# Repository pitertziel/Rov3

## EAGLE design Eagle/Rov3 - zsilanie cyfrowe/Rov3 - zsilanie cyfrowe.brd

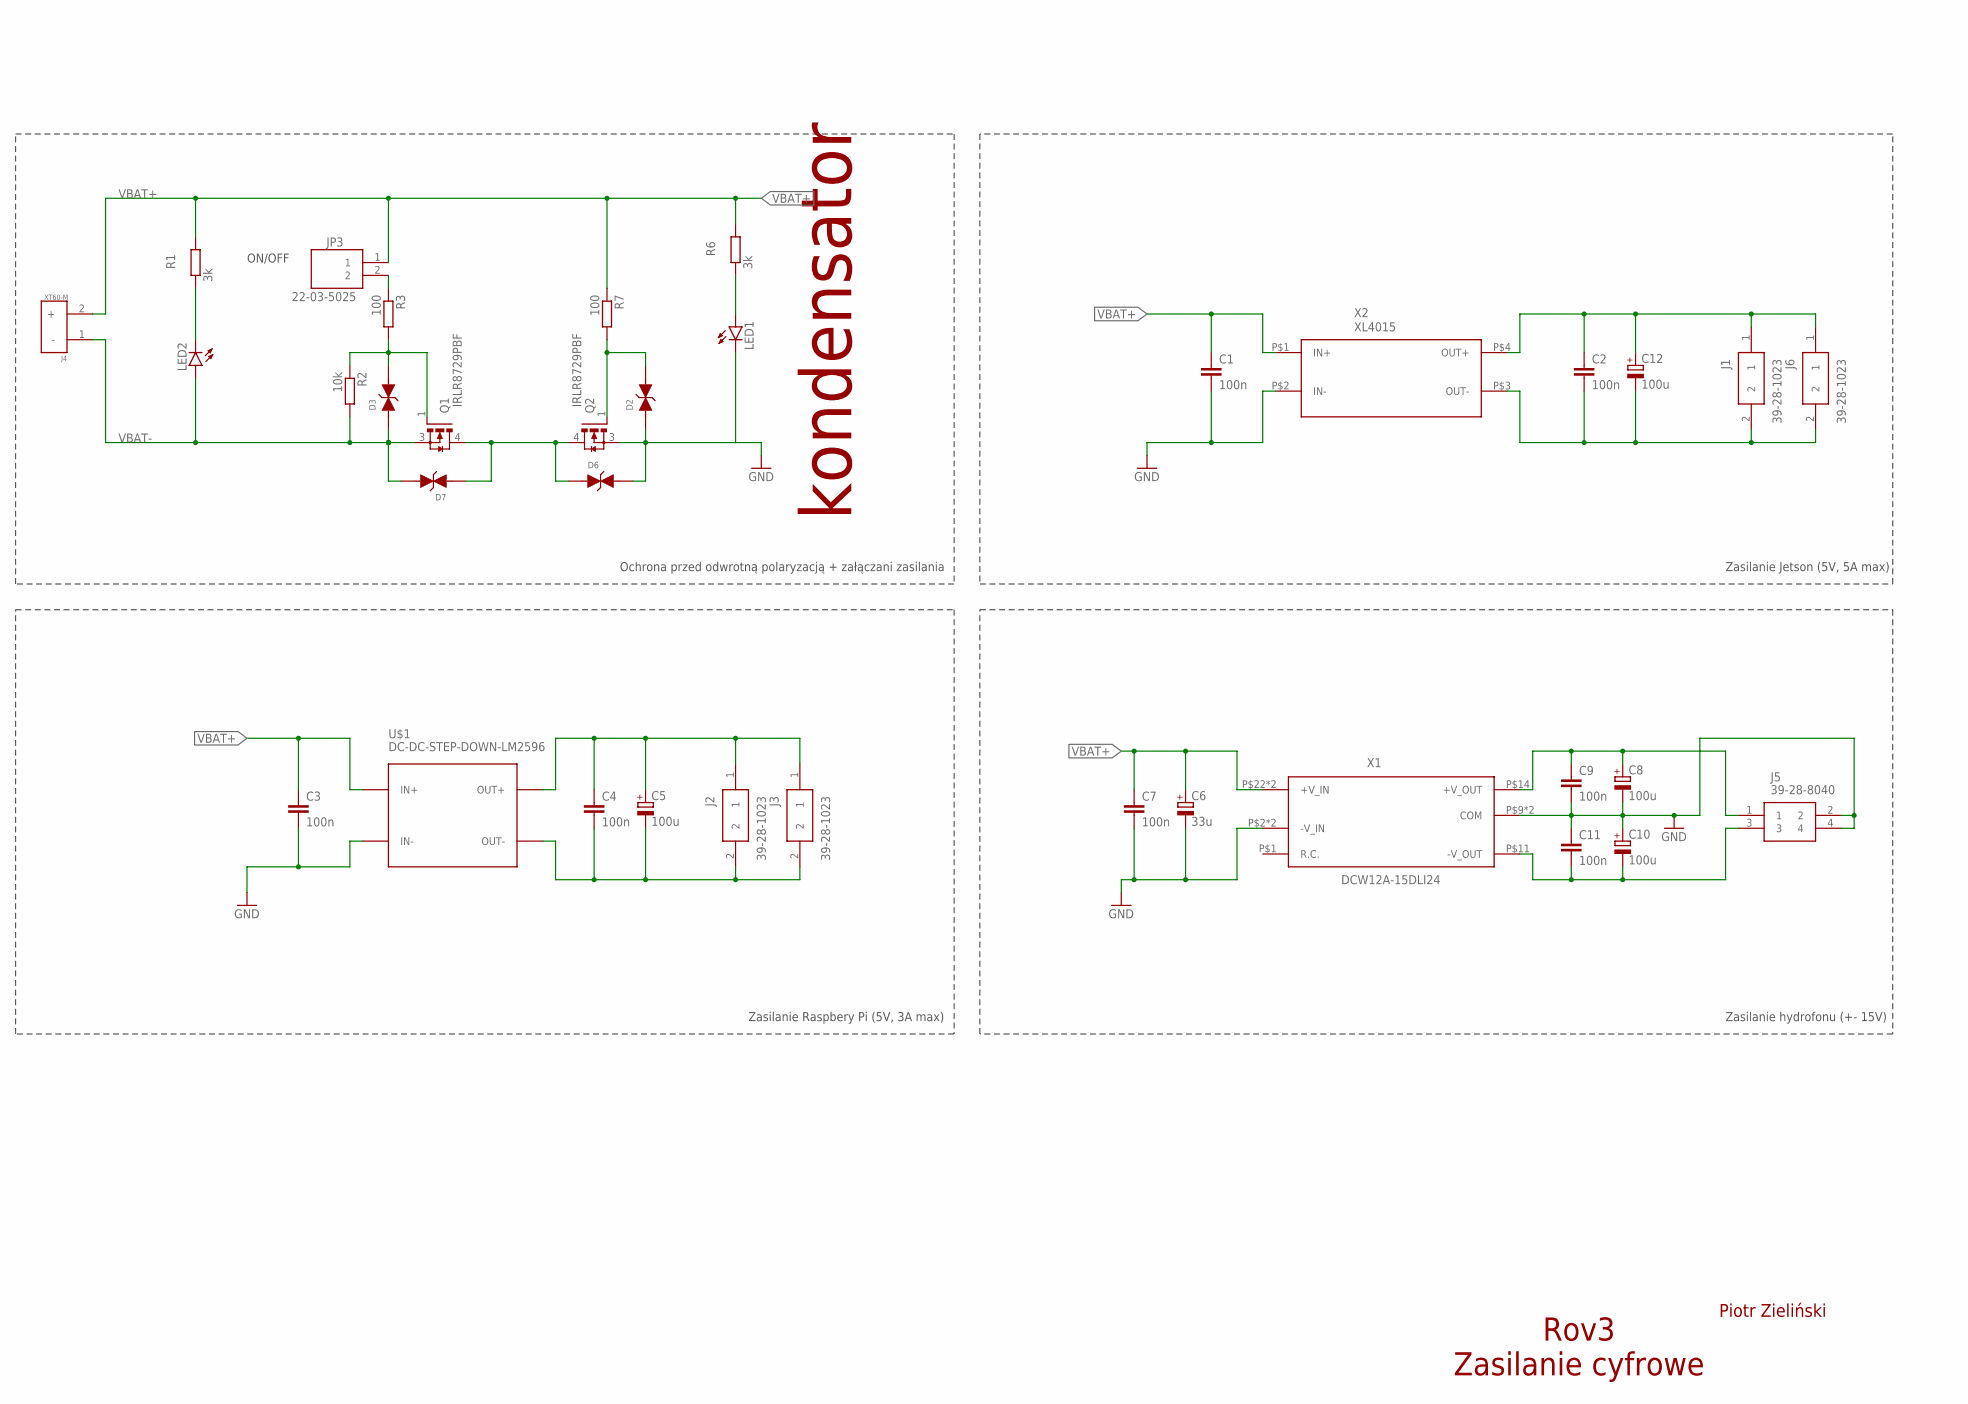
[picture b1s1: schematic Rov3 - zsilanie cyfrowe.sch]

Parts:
C1, C2, C3, C4, C7, C9, C11: 100n; C0805
C5, C8, C10, C12: 100u; E3,5-8
C6: 33u; E3,5-8
D2, D3, D6, D7: P6SMB20A_824501101; VARTVSP_SMA/DO-214AC
J1, J2, J3, J6: 39-28-1023; MOLEX_1X2_PCB_SOCKET
J4: XT60-M; AMASS_XT60-M
J5: 39-28-8040; MOLEX_2X2_PCB_SOCKET
JP3: 22-03-5025; 2.50MM_MINI-SPOX_2PIN_PCB_SOCKET
LED1, LED2: LEDCHIP-LED0805; CHIP-LED0805
Q1, Q2: IRLR8729PBF; DPAK
R1, R6: 3k; R1206
R2: 10k; R1206
R3, R7: 100; R1206
U$1: DC-DC-STEP-DOWN-LM2596
X1: DCW12A-15DLI24; DCW12A-15
X2: XL4015

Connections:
2596+: C4.1, C5.+, J2.1, J3.1, U$1.OUT+
2596-: C4.2, C5.-, J2.2, J3.2, U$1.OUT-
4015+: C2.1, C12.+, J1.1, J6.1, X2.P$4 (OUT+)
4015-: C2.2, C12.-, J1.2, J6.2, X2.P$3 (OUT-)
DCW_+15: C8.+, C9.1, J5.1, X1.P$14 (+V_OUT)
DCW_-15: C10.-, C11.2, J5.3, X1.P$11 (-V_OUT)
GND: C1.2, C3.2, C6.-, C7.2, C8.-, C9.2, C10.+, C11.1, D2.1, D6.2, J5.2, J5.4, LED1.C, Q2.3 (S), U$1.IN-, X1.P$2 (-V_IN), X1.P$3 (-V_IN), X1.P$9 (COM), X1.P$16 (COM), X2.P$2 (IN-)
unnamed: LED1.A, R6.1
unnamed: JP3.2, R3.1
unnamed: LED2.C, R1.1
Q1_G: D3.2, Q1.1 (G), R2.1, R3.2
Q1_Q2_D: D6.1, D7.1, Q1.4 (D), Q2.4 (D)
Q2G: D2.2, Q2.1 (G), R7.2
VBAT+: C1.1, C3.1, C6.+, C7.1, J4.2 (+), JP3.1, R1.2, R6.2, R7.1, U$1.IN+, X1.P$22 (+V_IN), X1.P$23 (+V_IN), X2.P$1 (IN+)
VBAT-: D3.1, D7.2, J4.1 (-), LED2.A, Q1.3 (S), R2.2

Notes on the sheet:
Rov3 Zasilanie cyfrowe
Piotr Zieliński
ON/OFF
kondensator
Ochrona przed odwrotną polaryzacją + załączani zasilania
Zasilanie Raspbery Pi (5V, 3A max)
Zasilanie Jetson (5V, 5A max)
Zasilanie hydrofonu (+- 15V)

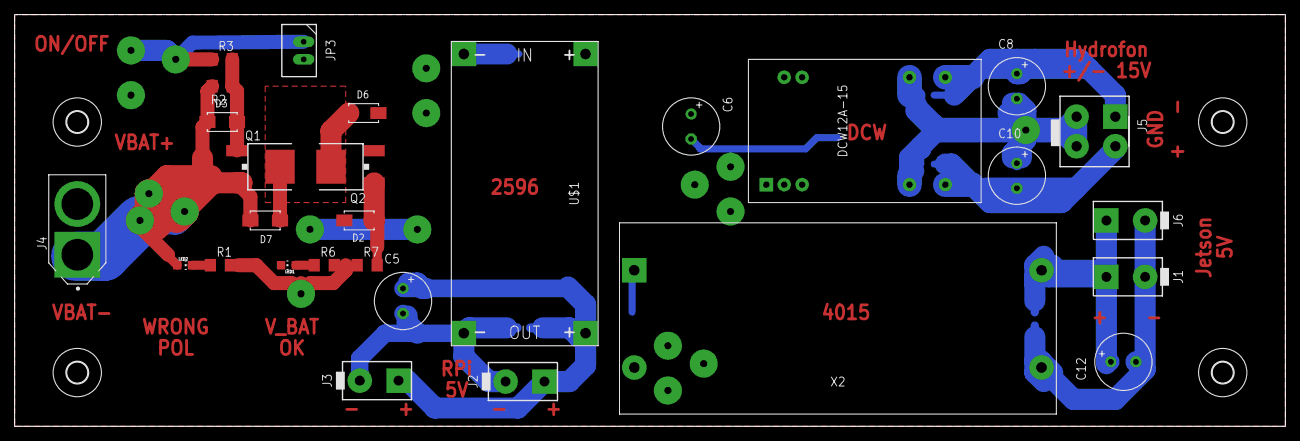
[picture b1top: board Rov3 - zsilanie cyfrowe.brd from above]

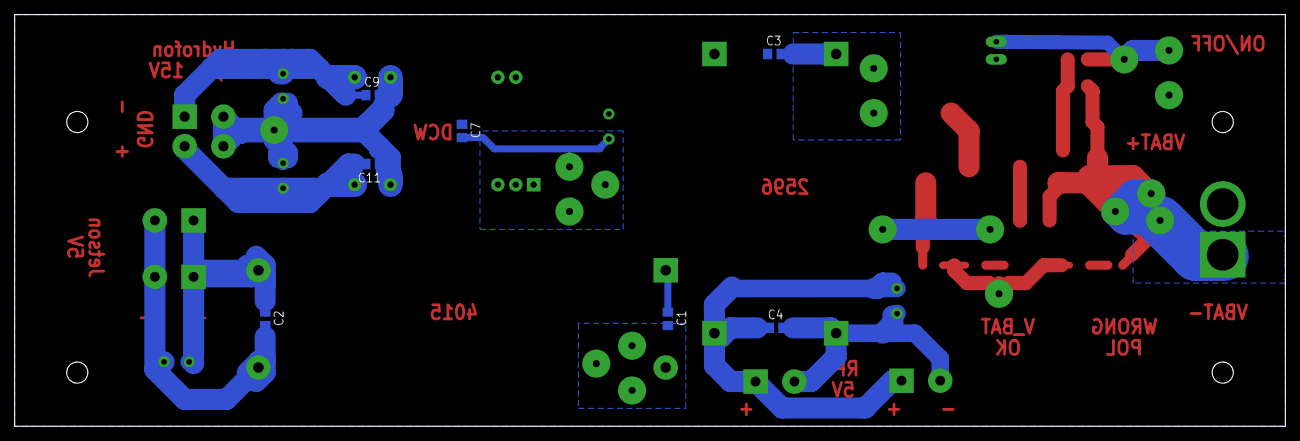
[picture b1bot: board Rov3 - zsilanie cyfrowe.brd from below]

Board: 2 copper layers, 180.3 x 58.4 mm, 39 parts (7 on the bottom side), 15 nets.

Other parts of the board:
U$2, U$3, U$4, U$5: 3,0

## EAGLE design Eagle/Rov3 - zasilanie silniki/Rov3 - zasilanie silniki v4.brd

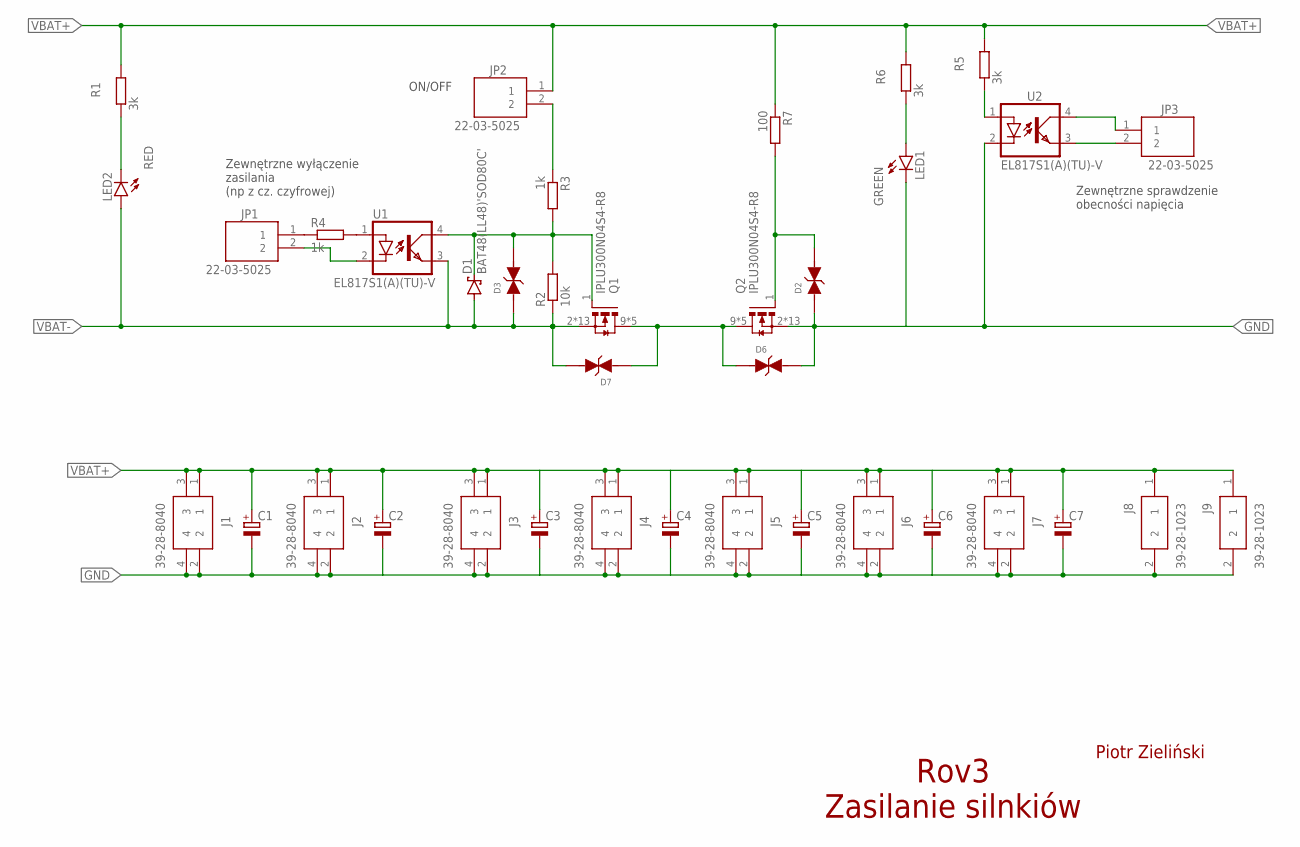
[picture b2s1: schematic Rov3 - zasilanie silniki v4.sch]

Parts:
C1, C2, C3, C4, C5, C6, C7: CPOL-EUE5-10.5; E5-10,5
D1: BAT48(LL48)'SOD80C'; SOD80C
D2, D3, D6, D7: P6SMB20A_824501101; VARTVSP_SMA/DO-214AC
J1, J2, J3, J4, J5, J6, J7: 39-28-8040; MOLEX_2X2_PCB_SOCKET
J8, J9: 39-28-1023; MOLEX_1X2_PCB_SOCKET
JP1, JP2, JP3: 22-03-5025; 2.50MM_MINI-SPOX_2PIN_PCB_SOCKET
LED1: GREEN; CHIP-LED0805
LED2: RED; CHIP-LED0805
Q1, Q2: IPLU300N04S4-R8; PG-HSOF-8-1
R1, R5, R6: 3k; R1206
R2: 10k; R1206
R3, R4: 1k; R1206
R7: 100; R1206
U1, U2: EL817S1(A)(TU)-V; SOIC254P1030X390-4N_EL817S1(A)(TU)-V

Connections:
GND: C1.-, C2.-, C3.-, C4.-, C5.-, C6.-, C7.-, D2.1, D6.2, J1.2, J1.4, J2.2, J2.4, J3.2, J3.4, J4.2, J4.4, J5.2, J5.4, J6.2, J6.4, J7.2, J7.4, J8.2, J9.2, LED1.C, Q2.2 (S), Q2.3 (S), Q2.4 (S), Q2.5 (S), Q2.6 (S), Q2.7 (S), Q2.8 (S), Q2.10 (S), Q2.11 (S), Q2.12 (S), Q2.13 (S), Q2.14 (S), Q2.15 (S), U2.2 (C)
unnamed: LED1.A, R6.1
unnamed: D6.1, D7.1, Q1.9 (D), Q1.16 (D), Q1.17 (D), Q1.18 (D), Q1.19 (D), Q2.9 (D), Q2.16 (D), Q2.17 (D), Q2.18 (D), Q2.19 (D)
unnamed: JP1.1, R4.1
unnamed: D1.C, D3.2, Q1.1 (G), R2.2, R3.2, U1.4 (COL)
unnamed: JP1.2, U1.2 (C)
unnamed: R4.2, U1.1 (A)
unnamed: JP2.2, R3.1
unnamed: JP3.2, U2.3 (EMIT)
unnamed: JP3.1, U2.4 (COL)
unnamed: R5.1, U2.1 (A)
unnamed: LED2.C, R1.1
unnamed: D2.2, Q2.1 (G), R7.2
VBAT+: C1.+, C2.+, C3.+, C4.+, C5.+, C6.+, C7.+, J1.1, J1.3, J2.1, J2.3, J3.1, J3.3, J4.1, J4.3, J5.1, J5.3, J6.1, J6.3, J7.1, J7.3, J8.1, J9.1, JP2.1, R1.2, R5.2, R6.2, R7.1
VBAT-: D1.A, D3.1, D7.2, LED2.A, Q1.2 (S), Q1.3 (S), Q1.4 (S), Q1.5 (S), Q1.6 (S), Q1.7 (S), Q1.8 (S), Q1.10 (S), Q1.11 (S), Q1.12 (S), Q1.13 (S), Q1.14 (S), Q1.15 (S), R2.1, U1.3 (EMIT)

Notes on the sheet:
Rov3 Zasilanie silnkiów
Piotr Zieliński
Zewnętrzne sprawdzenie obecności napięcia
ON/OFF
Zewnętrzne wyłączenie zasilania (np z cz. czyfrowej)

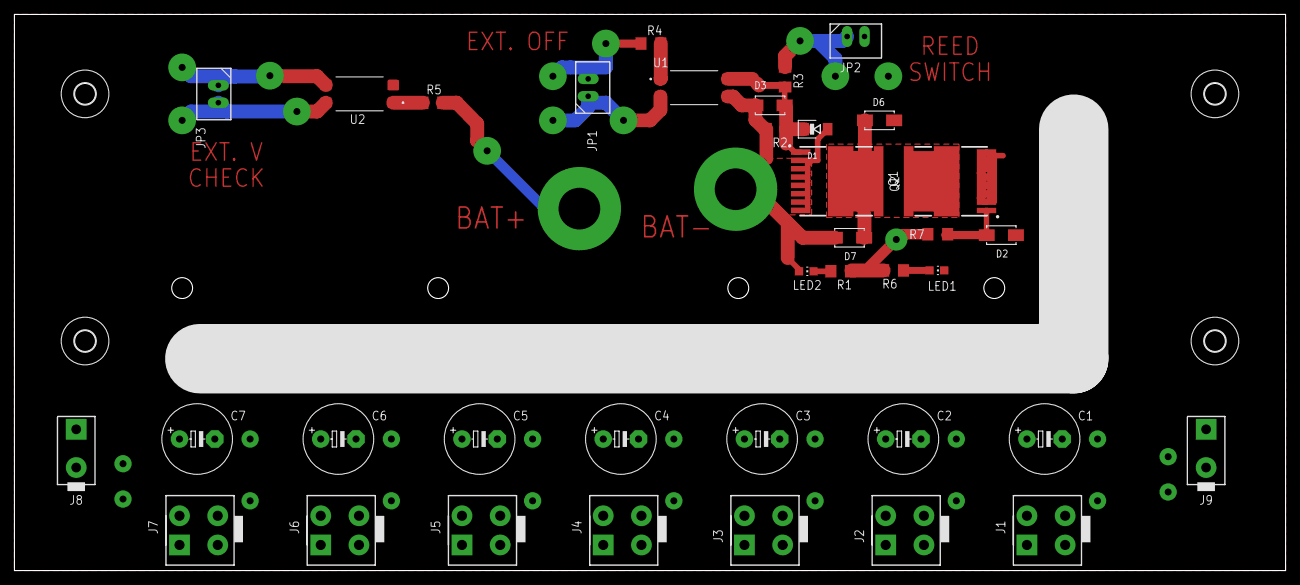
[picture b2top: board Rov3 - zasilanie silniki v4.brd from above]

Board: 2 copper layers, 182.9 x 80.0 mm, 41 parts (0 on the bottom side), 15 nets.

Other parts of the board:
U$1, U$2, U$3, U$4: 3,0

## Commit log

2019-05-06 Added old KiCad files
2019-05-07 Board outline
2019-05-07 Screenshot added
2019-06-19 Up to date version
2019-06-19 abcsda
2020-05-12 Added more documentation
